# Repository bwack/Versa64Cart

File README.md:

/pictures/logo.png)

Versa64Cart is designed to be a modern easy-to-use cartridge development board for Commodore 64 and Commodore 128 hobbyists and hackers. The versatile design of the PCB allows for flexible implementation of various cartridge types. Whether it’s a simple cartridge backup of an 8k game or a switchable multi-program diagnostic cartridge, Versa64Cart has you covered.

Supported EPROMS are: 27C64 (8k), 27C128 (16k), 27C256 (32k), 27C512 (64k).
Please see the documentation for more information.

I have put the rev 1.1 in a separate folder in case someone wants to use the kicad files as a template.
Rev. 1.2 and onwards is designed by [Sven Petersen](https://github.com/svenpetersen1965 "Sven's github repository!") in eagle. It is a complete redrawn schematic and layout.

Sven has designed another cartridge called [Diag64cart](https://github.com/svenpetersen1965/Diag64cart) derived from this project.

# Quick Guide

## Obtaining binaries

Use the cartconv.exe tool from the VICE emulator to get information and to extract the binary from .CRT files. Copy it to the same folder as your .CRT files.

List the .CRT information:

```
C:\cartconv>cartconv -f deadtest.CRT
CRT Version: 1.0
Name: C64DEADTESTREV718220
Hardware ID: 0 (Generic Cartridge)
Mode: exrom: 1 game: 0 (ultimax)

offset  sig  type  bank start size  chunklen
$000040 CHIP ROM   #000 $e000 $2000 $2010

total banks: 1 size: $002000
```
The hardware ID must be 0. The size of the eprom shown here is 8k ($2000).

Convert the binary:

`cartconv -i mycartridge.crt -o mycartridge.bin`

## Combining binaries

The Versa64Cart supports EPROMS from 8k to 8x8k or 4x16k. The easiest way to combine is to use the copy command (in Windows):

`copy /b DeadTest.bin + jupiterl.bin + SomeGame.bin combined.bin`

Special care must be taken if mix 8k and 16k images. The 8k binaries must be allocated in pairs:

`copy /b first8k.bin + second8k.bin + some16k.bin combined.bin`

## Documentation

For more information Please see the [pdf file](v1.6/pdf/Versa64cart_v1_6.pdf) in this repository.

## Pictures

# Changes
## 1.6
- Change: Notches added to fit the thefuturewas8bit.com stumpy cartridge case (not the button hole!)

## 1.5
- Change: Combined footprint SW1, 5Way-DIP and 2x5 2.54mm pin header

## 1.4
- Change: card edge connector with pads like in v1.1

## 1.3
- Change: Cartridge enclosure support
  - Moved IC socket away from edge
  - Moved diode group away from edge
  - Bom: Use right angle pin headers. The straight ones are too tall.
  
## 1.2
- A reset button
- Jumpers accessible on outer edge.*
- Solder jumpers at the top layer
- New documentation
- Designed in Eagle
* Remember to turn off the computer before changing the jumpers.

/pictures/Versa64Cart_scan_both_sides.jpg)

## 1.1 and 1.0

- Designed in KiCad based on simple64cart eagle files
- Support retro innovation cartridge enclosure (allthough pins too high)
- Moved IC sockets further from edge
- Added 16k game support
- Added dip switch and jumpers
- Added Documentation

# External websites

[Blog post, "Versa64Cart and C64 ROMs", by Gregory Nacu at c64os.com ](https://c64os.com/post/versa64cart)

# Versa64Cart on YouTube

https://www.youtube.com/results?search_query=Versa64Cart

# VersaZIF64
Check out VersaZIF64 if you are interested in the Versa64cart and with a ZIF socket.
https://github.com/bwack/VersaZIF64

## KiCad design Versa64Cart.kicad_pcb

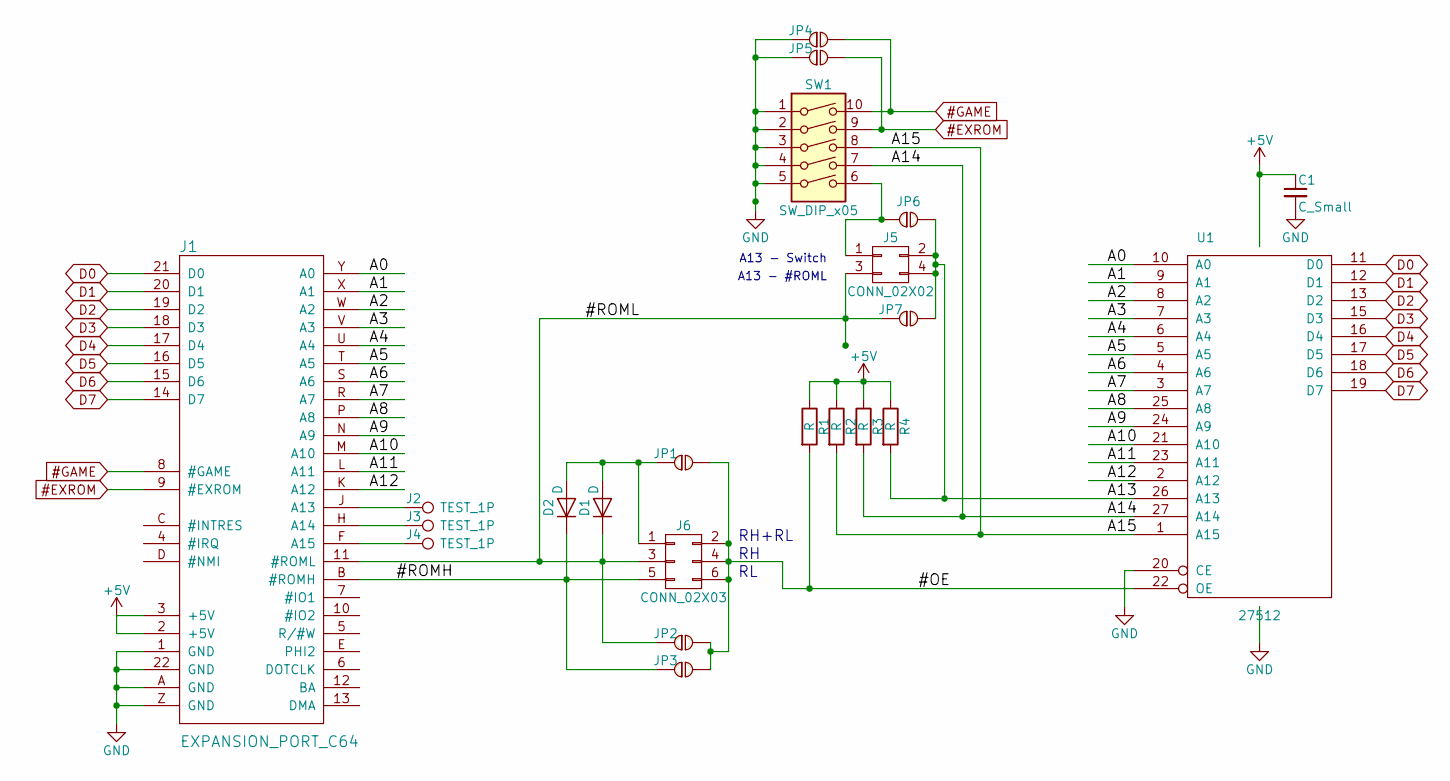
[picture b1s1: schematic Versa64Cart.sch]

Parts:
C1: C_Small; C_Disc_D3.8mm_W2.6mm_P2.50mm
D1, D2: D; D_DO-35_SOD27_P7.62mm_Horizontal
J1: EXPANSION_PORT_C64; C64_EXPANSION_PORT
J2, J3, J4: TEST_1P; PINTST
J5: CONN_02X02; Pin_Header_Straight_2x02_Pitch2.54mm
J6: CONN_02X03; Pin_Header_Straight_2x03_Pitch2.54mm
JP1, JP2, JP3, JP4, JP5, JP6, JP7: JUMPER_2-PIN; SOLDER-JUMPER_1-WAY
R1, R2, R3, R4: R; R_Axial_DIN0207_L6.3mm_D2.5mm_P7.62mm_Horizontal
SW1: SW_DIP_x05; SW_DIP_x5_W7.62mm_Slide
U1: 27512; DIP-28_W15.24mm_LongPads

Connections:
#EXROM: J1.9 (#EXROM), JP5.2, SW1.9
#GAME: J1.8 (#GAME), JP4.2, SW1.10
+5V: C1.1, J1.2 (+5V), J1.3 (+5V), R1.1, R2.1, R3.1, R4.1, U1.28 (VCC)
/#OE: J6.2, J6.4, J6.6, JP1.2, JP2.2, JP3.2, R1.2, U1.22 (OE)
/#ROMH: D2.1 (K), J1.B (#ROMH), J6.5, JP3.1
/#ROML: D1.1 (K), J1.11 (#ROML), J5.3, J6.3, JP2.1, JP7.1
/A0: J1.Y (A0), U1.10 (A0)
/A1: J1.X (A1), U1.9 (A1)
/A2: J1.W (A2), U1.8 (A2)
/A3: J1.V (A3), U1.7 (A3)
/A4: J1.U (A4), U1.6 (A4)
/A5: J1.T (A5), U1.5 (A5)
/A6: J1.S (A6), U1.4 (A6)
/A7: J1.R (A7), U1.3 (A7)
/A8: J1.P (A8), U1.25 (A8)
/A9: J1.N (A9), U1.24 (A9)
/A10: J1.M (A10), U1.21 (A10)
/A11: J1.L (A11), U1.23 (A11)
/A12: J1.K (A12), U1.2 (A12)
/A13: J5.2, J5.4, JP6.2, JP7.2, R4.2, U1.26 (A13)
/A14: R3.2, SW1.7, U1.27 (A14)
/A15: R2.2, SW1.8, U1.1 (A15)
D0: J1.21 (D0), U1.11 (D0)
D1: J1.20 (D1), U1.12 (D1)
D2: J1.19 (D2), U1.13 (D2)
D3: J1.18 (D3), U1.15 (D3)
D4: J1.17 (D4), U1.16 (D4)
D5: J1.16 (D5), U1.17 (D5)
D6: J1.15 (D6), U1.18 (D6)
D7: J1.14 (D7), U1.19 (D7)
GND: C1.2, J1.1 (GND), J1.22 (GND), J1.A (GND), J1.Z (GND), JP4.1, JP5.1, SW1.1, SW1.2, SW1.3, SW1.4, SW1.5, U1.14 (GND), U1.20 (CE)
unnamed: D1.2 (A), D2.2 (A), J6.1, JP1.1
unnamed: J1.F (A15), J4.1
unnamed: J1.H (A14), J3.1
unnamed: J1.J (A13), J2.1
unnamed: J5.1, JP6.1, SW1.6

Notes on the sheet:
A13 - #ROML
A13 - Switch
RH+RL

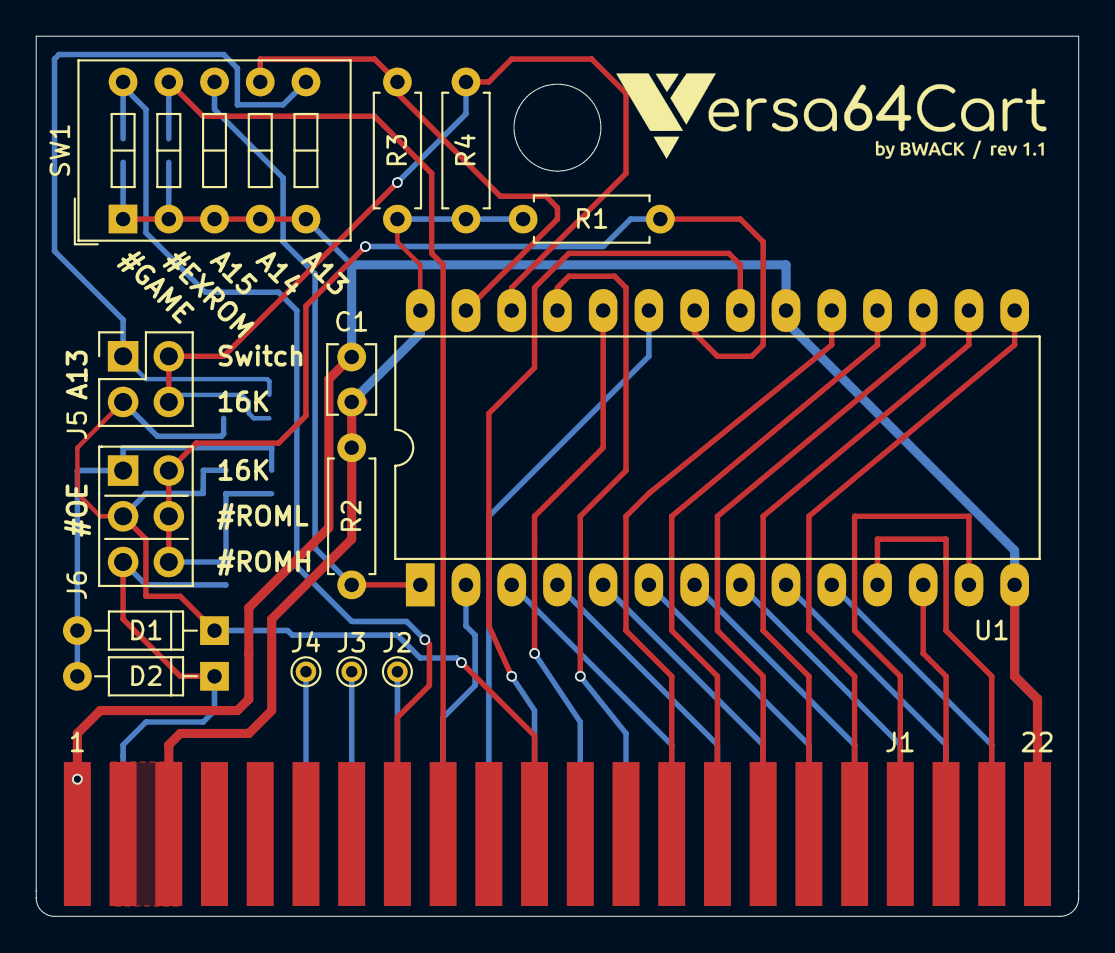
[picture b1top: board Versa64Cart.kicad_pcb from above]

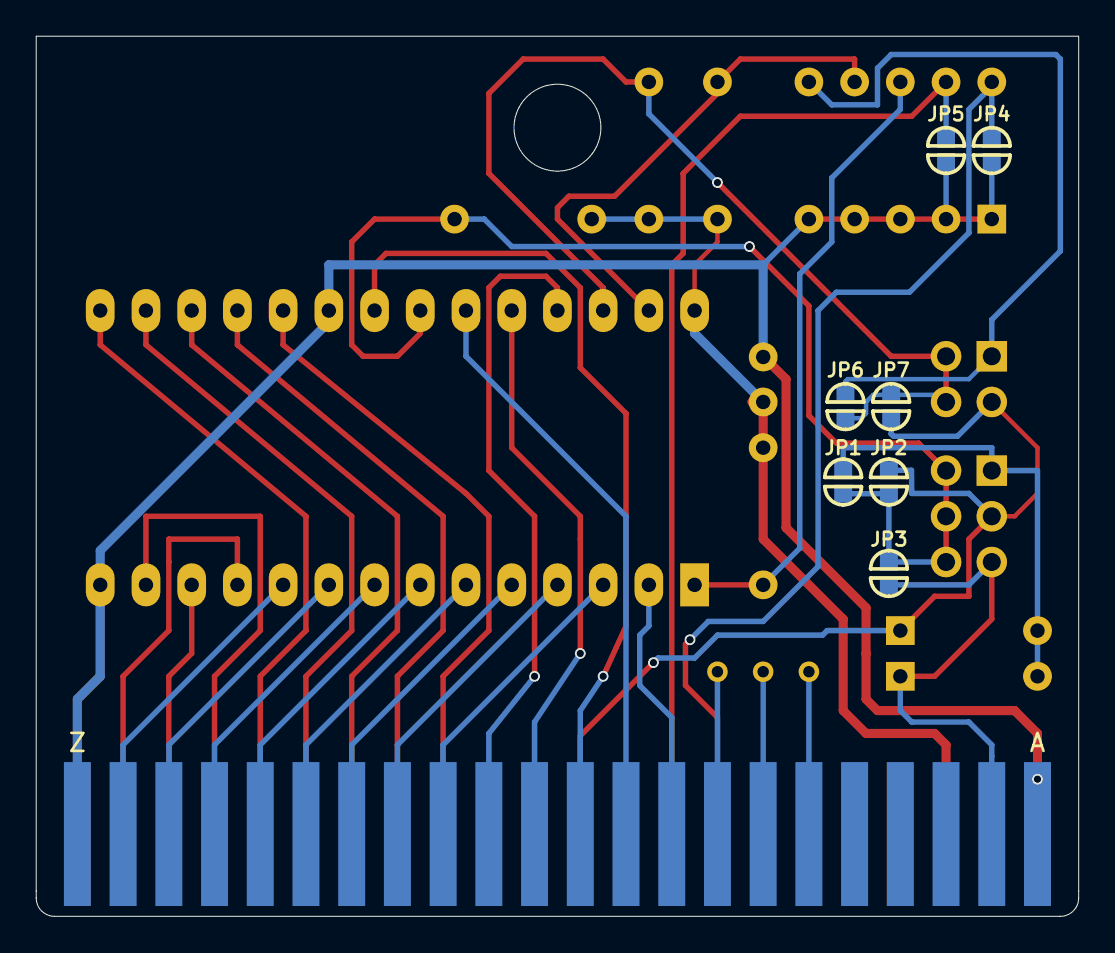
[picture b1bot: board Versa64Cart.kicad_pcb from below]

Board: 2 copper layers, 57.9 x 48.9 mm, 22 parts (7 on the bottom side), 36 nets.

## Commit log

2017-06-27 :tada: Added .gitattributes & .gitignore files
2017-06-27 first commit 1.0
2017-06-27 3D render
2017-06-27 the pcb image file
2017-06-27 changed NPTH pad to be NP
2017-06-27 NPTH NP
2017-06-29 VersaCart logo
2017-07-22 Rev 1.1 - missing trace on ROML
2017-09-08 User Guide, not finished
2017-09-08 User Guide
2017-09-08 User guide V0.11
2017-09-08 User Guide V0.12
2017-09-08 User Guide V0.13
2017-09-08 User Guide V0.14
2017-09-09 User Guide V.15 DIP switches
2017-09-11 User Guide V0.16
2017-09-27 gerbers
    tested with dirtypcbs. No extended attributes to support chinese fabs
    with CAM350 software.
2017-09-27 User Guide V0.17 minor changes
2018-01-08 vet ikke hvorfor denne endret seg
2018-01-08 100nF
2018-04-17 online bom #1
2018-05-06 User Guide V0.18: Board dimentions and enclosures.
2018-09-22 Change: Documentation, dead test example. Using large eprom with single 8k image.
2018-09-22 Change: Docs/dead test cart example. Using eprom larger than 27C64 #4
2018-09-22 Change: Docs/Other notes: does kernal roms on the cartridge work #3
2019-04-18 Removed Gerbers catalogue with incorrect gerber file #5
    There is a gerbers.zip file though
2019-05-25 Include v1.2 from Sven
2019-05-25 Released Rev. 1.2
    Rev. 1.2 adds some cosmetic changes to Rev 1.1. The jumpers have been moved to the outer edge of the board and a reset switch has been added.
2019-05-26 readme in v1.1
2019-05-30 new v1.3 files and readme
2019-05-30 changed to right angle pinheaders
2019-05-30 right angle pinheaders in docs and bom
2019-05-30 comma separate file
    github didn't like the colon separated file.
2019-05-30 no idea
2019-06-25 Rev 1.4
2019-11-23 Updated readme with info on combining binaries #11
2019-11-27 Add files via upload
    Enhanced the documentation. Chapter about merging more than one *.bin to an image.bin for the eprom. Module description v1.4a
2019-11-27 Add files via upload
    Added the pictures for the extended documentation.
2020-05-07 combined footprint SW1, 5way DIP switch and 2x5 way 2.54mm pin header
2020-10-18 Updated documentation (pdf). Fixed mistake in table on page 7. #16
2021-12-20 v1.6: added notches for the stumpy cart
2021-12-20 readme update
